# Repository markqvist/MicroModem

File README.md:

MicroModem - Deprecated Firmware
==========

*Please note that the firmware in this repo is deprecated! For a newer, much better general purpose firmware, use [MicroModemGP](https://github.com/markqvist/MicroModemGP). For an APRS-oriented firmware use [MicroAPRS](https://github.com/markqvist/MicroAPRS)*

*There is now a completely reworked hardware and software platform based on the legacy of MicroModem, called [OpenModem](https://github.com/markqvist/openmodem/), with many more features and a more flexible implementation.*

MicroModem is an educational implementation of a 1200-baud AFSK modem. This implementation is targeted at the Atmega 328p microprocessor used in many Arduino boards and spinoffs. It can be build very easily with an Arduino board based on the Atmega 328p, and around 15 common electronics components.

Please read the "Quickstart.pdf" in the Documentation folder for some pointers on building the modem!

If you want to use MicroModem for APRS, check out the [MicroAPRS](https://github.com/markqvist/MicroAPRS). This fork is created specifically for APRS.

The repository contains schematics and Eagle PCB files for a Microduino module. There is also fritzing sketches for both an Arduino shield and a Microduino module, with notes so they are easier to understand. I have had the eagle PCB fabricated, and it is working great, so you can use that if want to make your own board.

I am currently writing an illustrated tutorial to go along with the source-code, but even now, the source code is extremely well documented, and all the concepts are explained in great detail in the comments.

By default MicroModem uses a very simple protocol dubbed MP1. The protocol enables end-to-end transport with forward error-correction and compression. Compression is courtesy of the excellent [Heatshrink](https://github.com/atomicobject/heatshrink) library. MP1 can also encapsulate TCP/IP traffic from a host computer with SLIP.

MicroModem was created as an easy to build, low-cost and very flexible radio-modem. It also supports the AX.25 implementation in BertOS, so it can be used with that for APRS and the likes very easily.

While this project is based on Arduino hardware, it does not use the Arduino IDE. The project has been implemented in your normal C with makefile style, and uses libraries from the open source BertOS.

Visit [my site](http://unsigned.io) for questions, comments and other details.

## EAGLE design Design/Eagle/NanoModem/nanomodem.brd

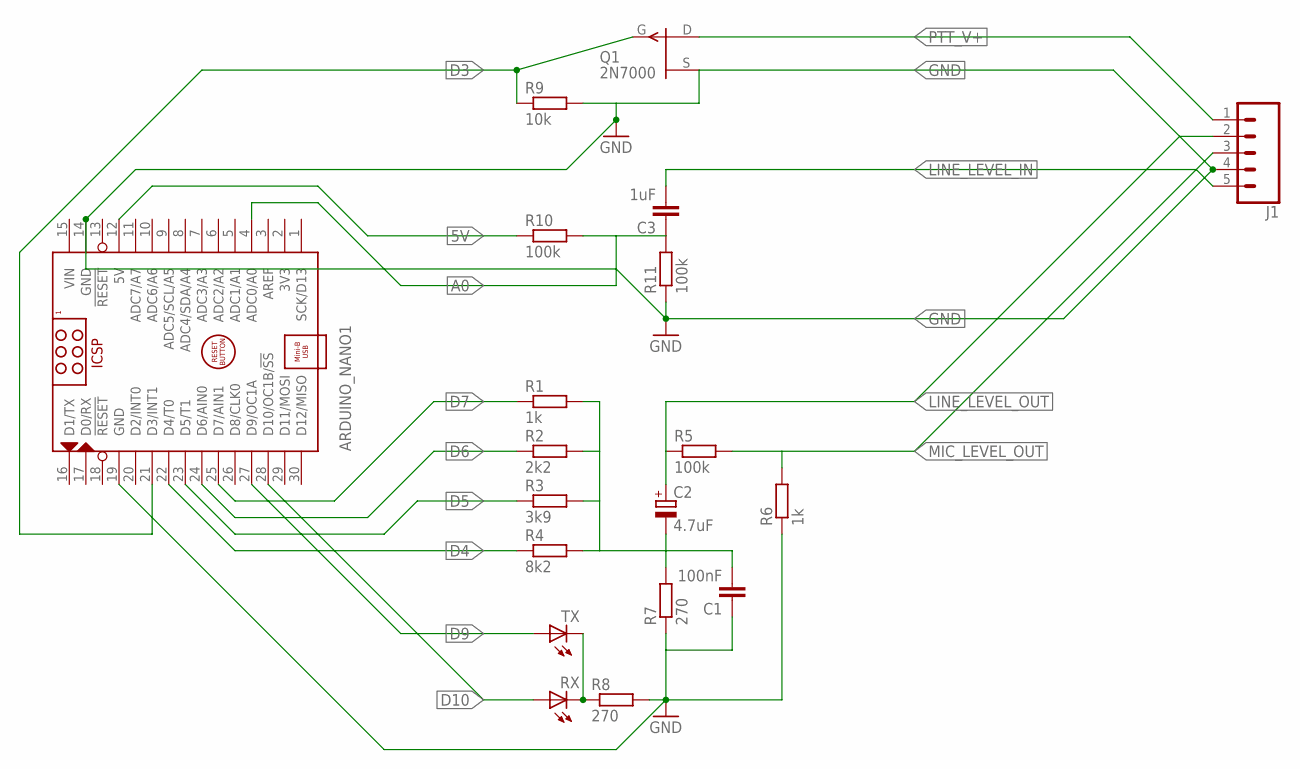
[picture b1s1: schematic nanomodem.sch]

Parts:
ARDUINO_NANO1: ARDUINO_NANO
C1: 100nF; C2.5-2
C2: 4.7uF; E2,5-4R
C3: 1uF; C2.5-2
J1: CONN_05; 1X05
Q1: 2N7000; TO92_MOD
R1, R6: 1k; 0204V
R2: 2k2; 0204V
R3: 3k9; 0204V
R4: 8k2; 0204V
R5, R10, R11: 100k; 0204V
R7, R8: 270; 0204V
R9: 10k; 0204V
RX: LED_ELD260; LED_LD260
TX: LED_ELD260; LED_LD260

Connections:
5V: ARDUINO_NANO1.12 (5V), R10.1
A0: ARDUINO_NANO1.4 (ADC0/A0), C3.1, R10.2, R11.2
D3: ARDUINO_NANO1.21 (D3/INT1), Q1.2 (G), R9.1
D4: ARDUINO_NANO1.22 (D4/T0), R4.1
D5: ARDUINO_NANO1.23 (D5/T1), R3.1
D6: ARDUINO_NANO1.24 (D6/AIN0), R2.1
D7: ARDUINO_NANO1.25 (D7/AIN1), R1.1
D9: ARDUINO_NANO1.27 (D9/OC1A), TX.A
D10: ARDUINO_NANO1.28 (D10/OC1B/!SS), RX.A
GND: ARDUINO_NANO1.14 (GND), ARDUINO_NANO1.19 (GND), C1.1, J1.4, Q1.3 (D), R6.1, R7.1, R8.2, R9.2, R11.1
LINE_LEVEL_IN: C3.2, J1.5
LINE_LEVEL_OUT: C2.+, J1.2, R5.1
MIC_LEVEL_OUT: J1.3, R5.2, R6.2
unnamed: R8.1, RX.K (C), TX.K (C)
unnamed: C1.2, C2.-, R1.2, R2.2, R3.2, R4.2, R7.2
PTT_V+: J1.1, Q1.1 (S)
VIN: ARDUINO_NANO1.15 (VIN)

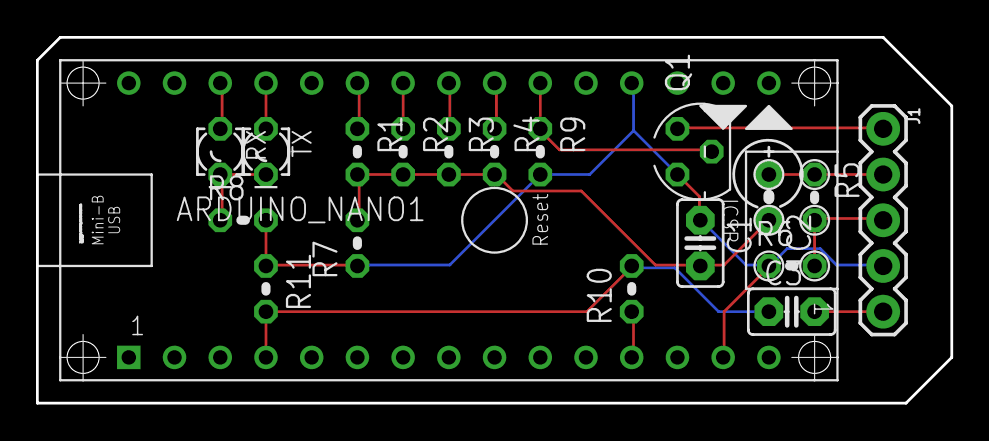
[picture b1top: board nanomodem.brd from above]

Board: 2 copper layers, 50.8 x 20.3 mm, 19 parts (0 on the bottom side), 16 nets.

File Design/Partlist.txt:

Partlist

Exported from Modem.sch at 9/18/14 8:45 PM

EAGLE Version 6.5.0 Copyright (c) 1988-2013 CadSoft

Assembly variant: 

Part           Value          Device         Package   Library        Sheet

C1             100nF          C2.5/2         C2.5-2    capacitor      1
C2             4.7uF          CPOL-EUE2.5-5V E2,5-4R   capacitor-pol  1
C3             1uF            C2.5/2         C2.5-2    capacitor      1
Q1             2N7000         2N7000         TO92      transistor     1
R1             1k             R-EU_0204/2V   0204V     resistor       1
R2             2k2            R-EU_0204/2V   0204V     resistor       1
R3             3k9            R-EU_0204/2V   0204V     resistor       1
R4             8k2            R-EU_0204/2V   0204V     resistor       1
R5             100k           R-EU_0204/2V   0204V     resistor       1
R6             1k             R-EU_0204/2V   0204V     resistor       1
R7             270            R-EU_0204/2V   0204V     resistor       1
R8             270            R-EU_0204/2V   0204V     resistor       1
R9             10k            R-EU_0204/2V   0204V     rcl            1
R10            100k           R-EU_0204/2V   0204V     rcl            1
R11            100k           R-EU_0204/2V   0204V     rcl            1
RX                            LED_ELD260     LED_LD260 eagle-ltspice  1
TX                            LED_ELD260     LED_LD260 eagle-ltspice  1

RADIO                         PINHD-1X3      1X03      adafruit       1
MICRODUINO_BTM                PINHD-1X9      1X09-BIG  adafruit       1
MICRODUINO_LFT                PINHD-1X9      1X09-BIG  adafruit       1
MICRODUINO_TOP                PINHD-1X9      1X09-BIG  adafruit       1
PTT+                          PINHD-1X1      1X01      adafruit       1
PTT-                          PINHD-1X1      1X01      adafruit       1

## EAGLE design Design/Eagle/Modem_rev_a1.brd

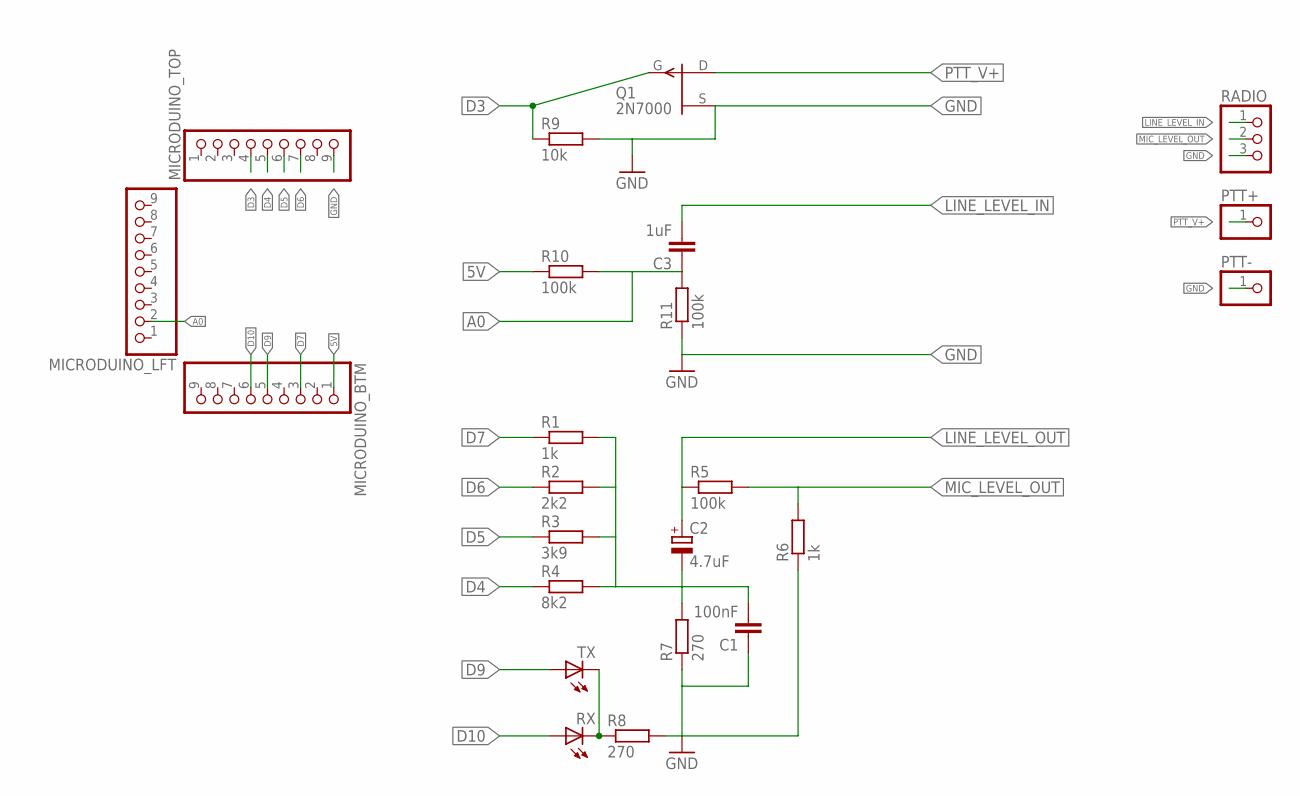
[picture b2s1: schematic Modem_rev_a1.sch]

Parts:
C1: 100nF; C2.5-2
C2: 4.7uF; E2,5-4R
C3: 1uF; C2.5-2
MICRODUINO_BTM: PINHD-1X9; 1X09-MICRODUINO
MICRODUINO_LFT: PINHD-1X9; 1X09-MICRODUINO
MICRODUINO_TOP: PINHD-1X9; 1X09-MICRODUINO
PTT+: PINHD-1X1; 1X01
PTT-: PINHD-1X1; 1X01
Q1: 2N7000; TO92_MOD
R1, R6: 1k; 0204V
R2: 2k2; 0204V
R3: 3k9; 0204V
R4: 8k2; 0204V
R5, R10, R11: 100k; 0204V
R7, R8: 270; 0204V
R9: 10k; 0204V
RADIO: PINHD-1X3; 1X03
RX: LED_ELD260; LED_LD260
TX: LED_ELD260; LED_LD260

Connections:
5V: MICRODUINO_BTM.1, R10.1
A0: C3.1, MICRODUINO_LFT.2, R10.2, R11.2
D3: MICRODUINO_TOP.4, Q1.2 (G), R9.1
D4: MICRODUINO_TOP.5, R4.1
D5: MICRODUINO_TOP.6, R3.1
D6: MICRODUINO_TOP.7, R2.1
D7: MICRODUINO_BTM.3, R1.1
D9: MICRODUINO_BTM.5, TX.A
D10: MICRODUINO_BTM.6, RX.A
GND: C1.1, MICRODUINO_TOP.9, PTT-.1, Q1.3 (D), R6.1, R7.1, R8.2, R9.2, R11.1, RADIO.3
LINE_LEVEL_IN: C3.2, RADIO.1
LINE_LEVEL_OUT: C2.+, R5.1
MIC_LEVEL_OUT: R5.2, R6.2, RADIO.2
unnamed: R8.1, RX.K (C), TX.K (C)
unnamed: C1.2, C2.-, R1.2, R2.2, R3.2, R4.2, R7.2
PTT_V+: PTT+.1, Q1.1 (S)

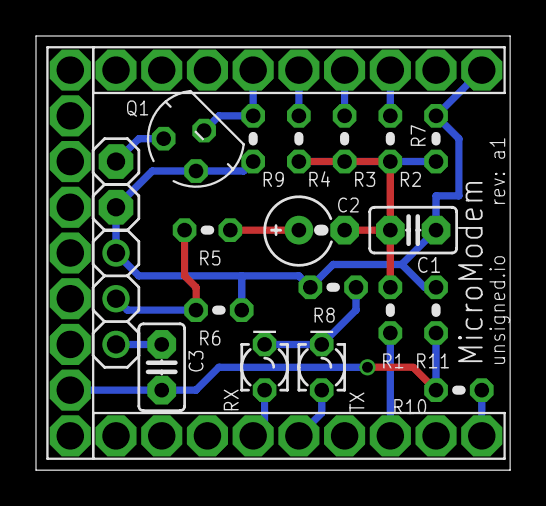
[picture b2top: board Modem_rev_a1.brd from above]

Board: 2 copper layers, 26.3 x 24.1 mm, 23 parts (0 on the bottom side), 16 nets.

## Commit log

2014-06-05 Added picture
2014-06-19 Update build
2014-09-18 Added partlist
2014-10-06 Minor stuff
2014-11-11 Design updates
2018-02-12 Added Arduino Nano board layout variant.
2018-02-12 Added note regarding Nano addition
2018-02-12 Revert "Added note regarding Nano addition"
    This reverts commit ea97561f06e2092306a496767b05dbe7994e39e3.

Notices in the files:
parts and their libraries:
SparkFun-Connectors: Licensing: Creative Commons ShareAlike 4.0 International - https://creativecommons.org/licenses/by-sa/4.0
